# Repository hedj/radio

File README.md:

radio
=====

A minimal software-defined radio, based on the GreenArrays GA144A12 microprocessor.
Provision is made for connection to a Raspberry Pi B+ and shields. The GA144 analog
i/o pins are brought out to pin-headers to allow for different choices of RF frontends.

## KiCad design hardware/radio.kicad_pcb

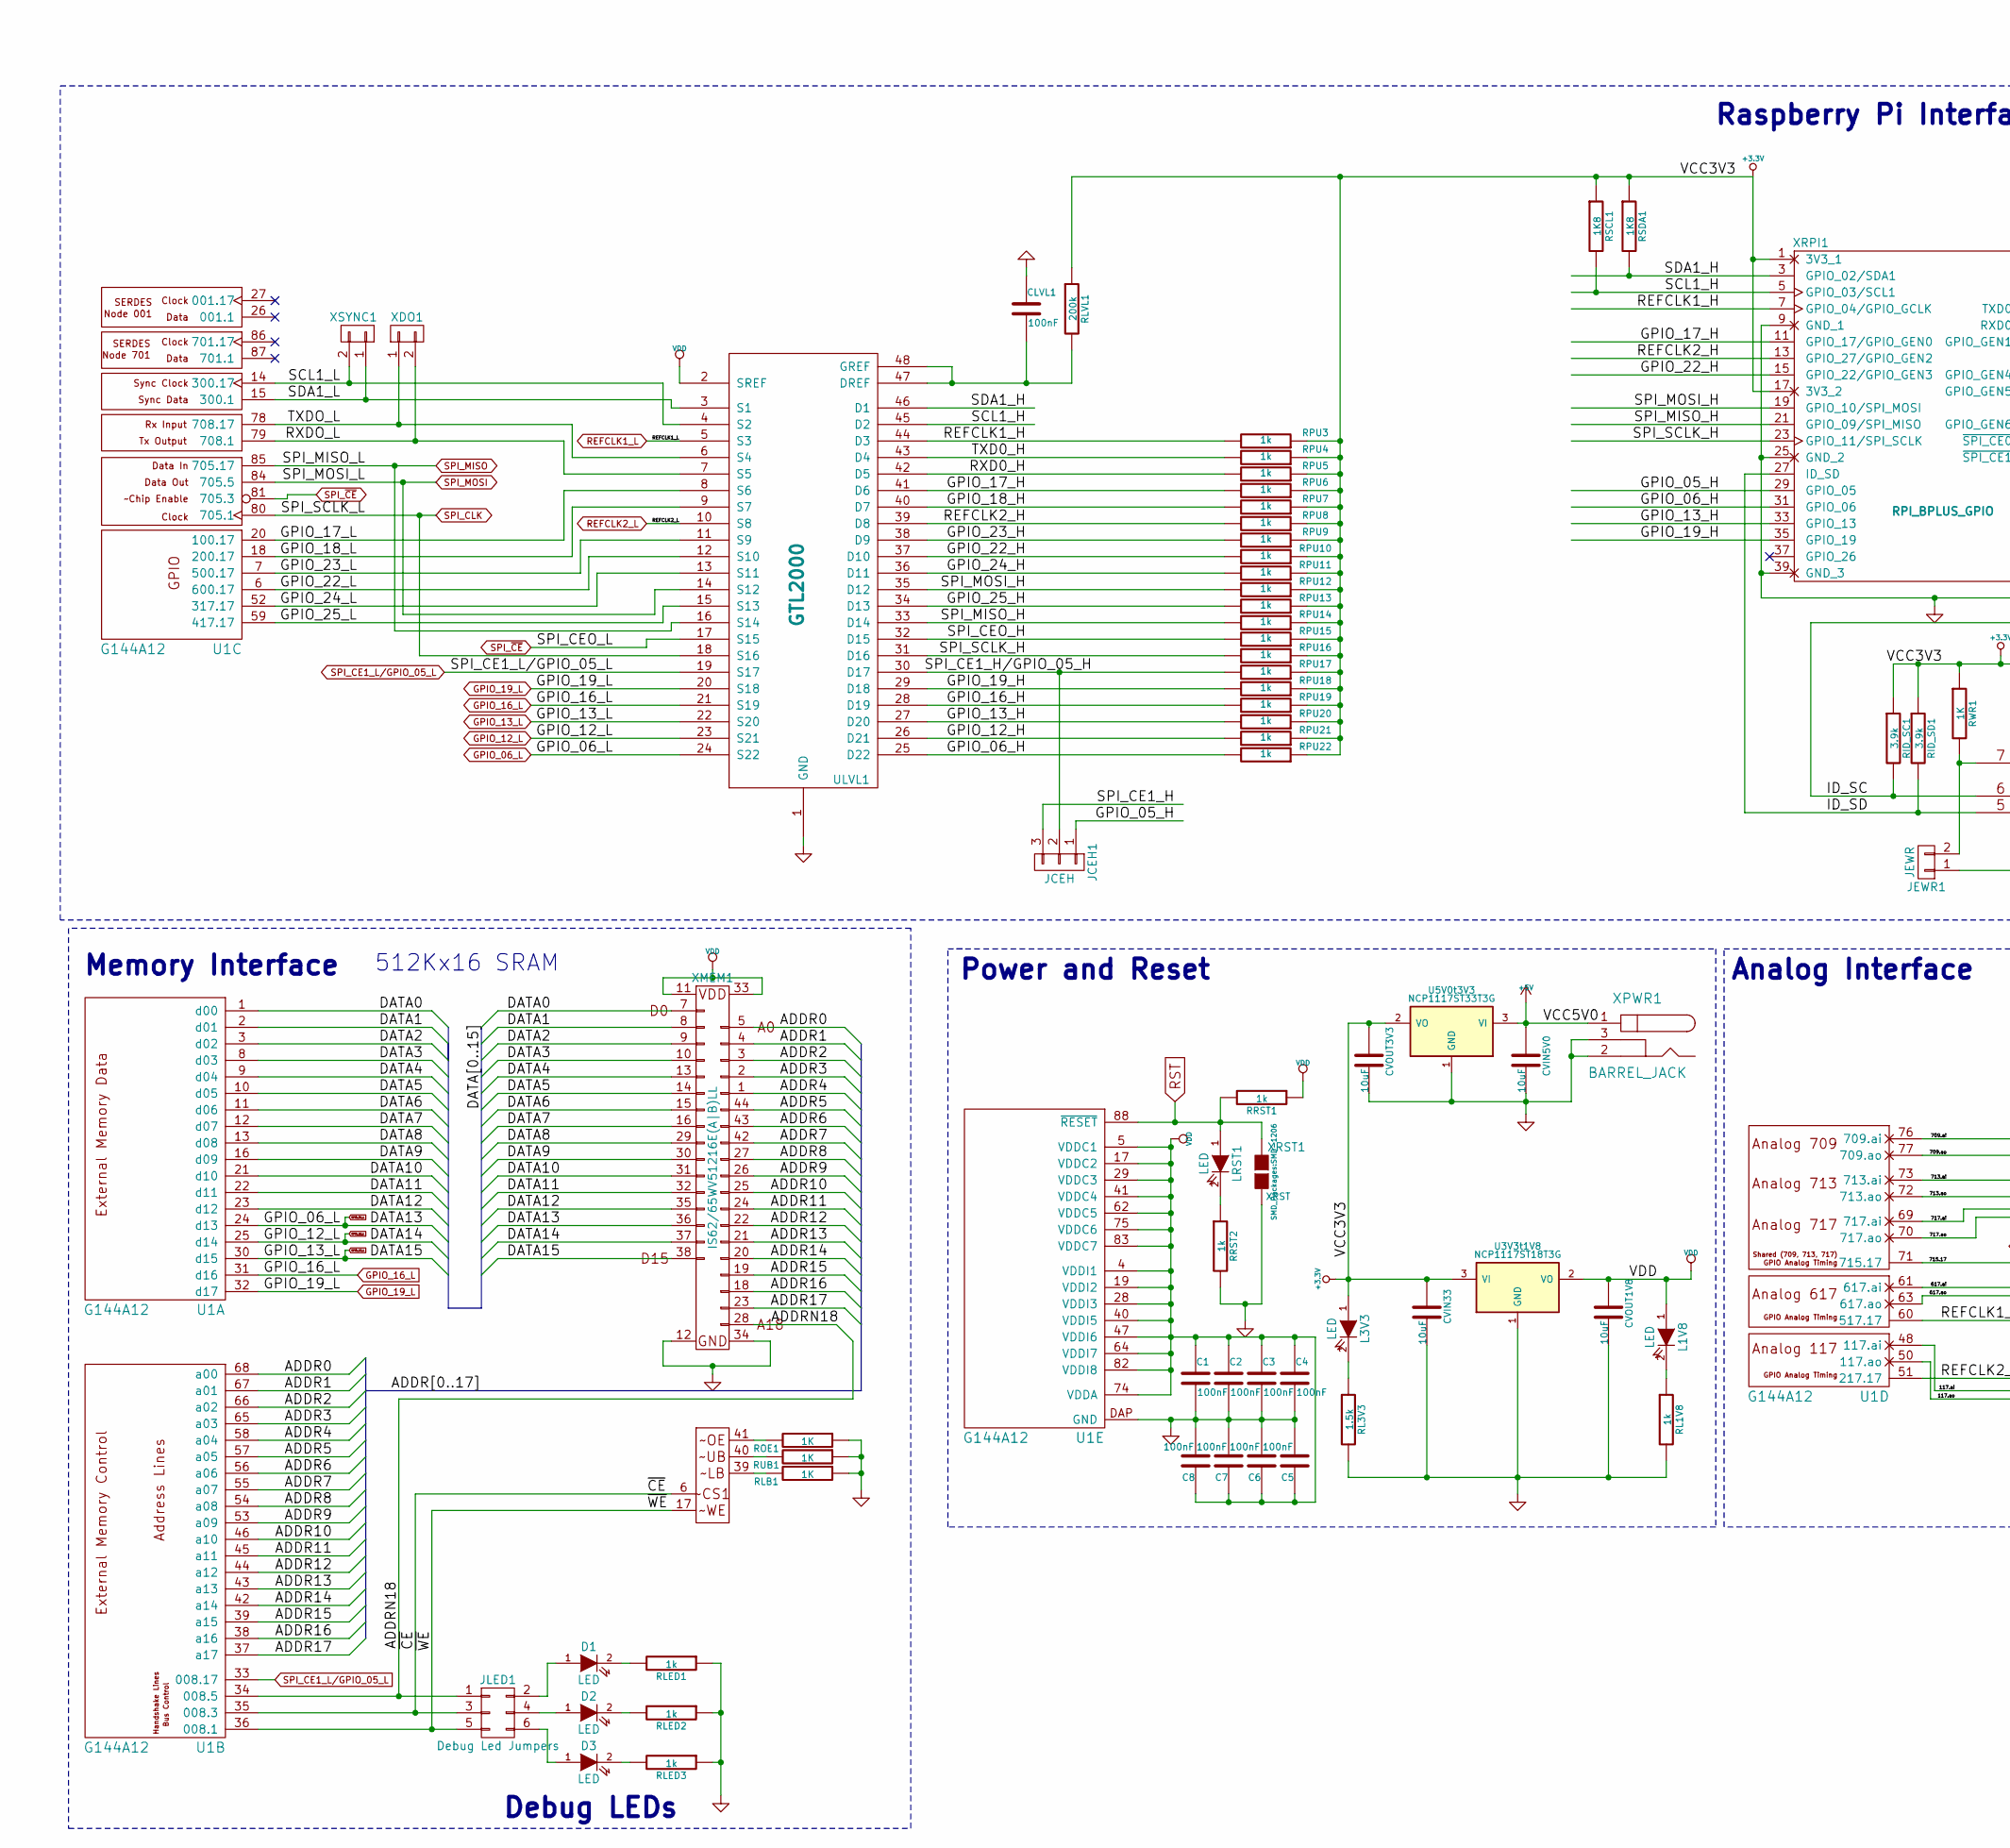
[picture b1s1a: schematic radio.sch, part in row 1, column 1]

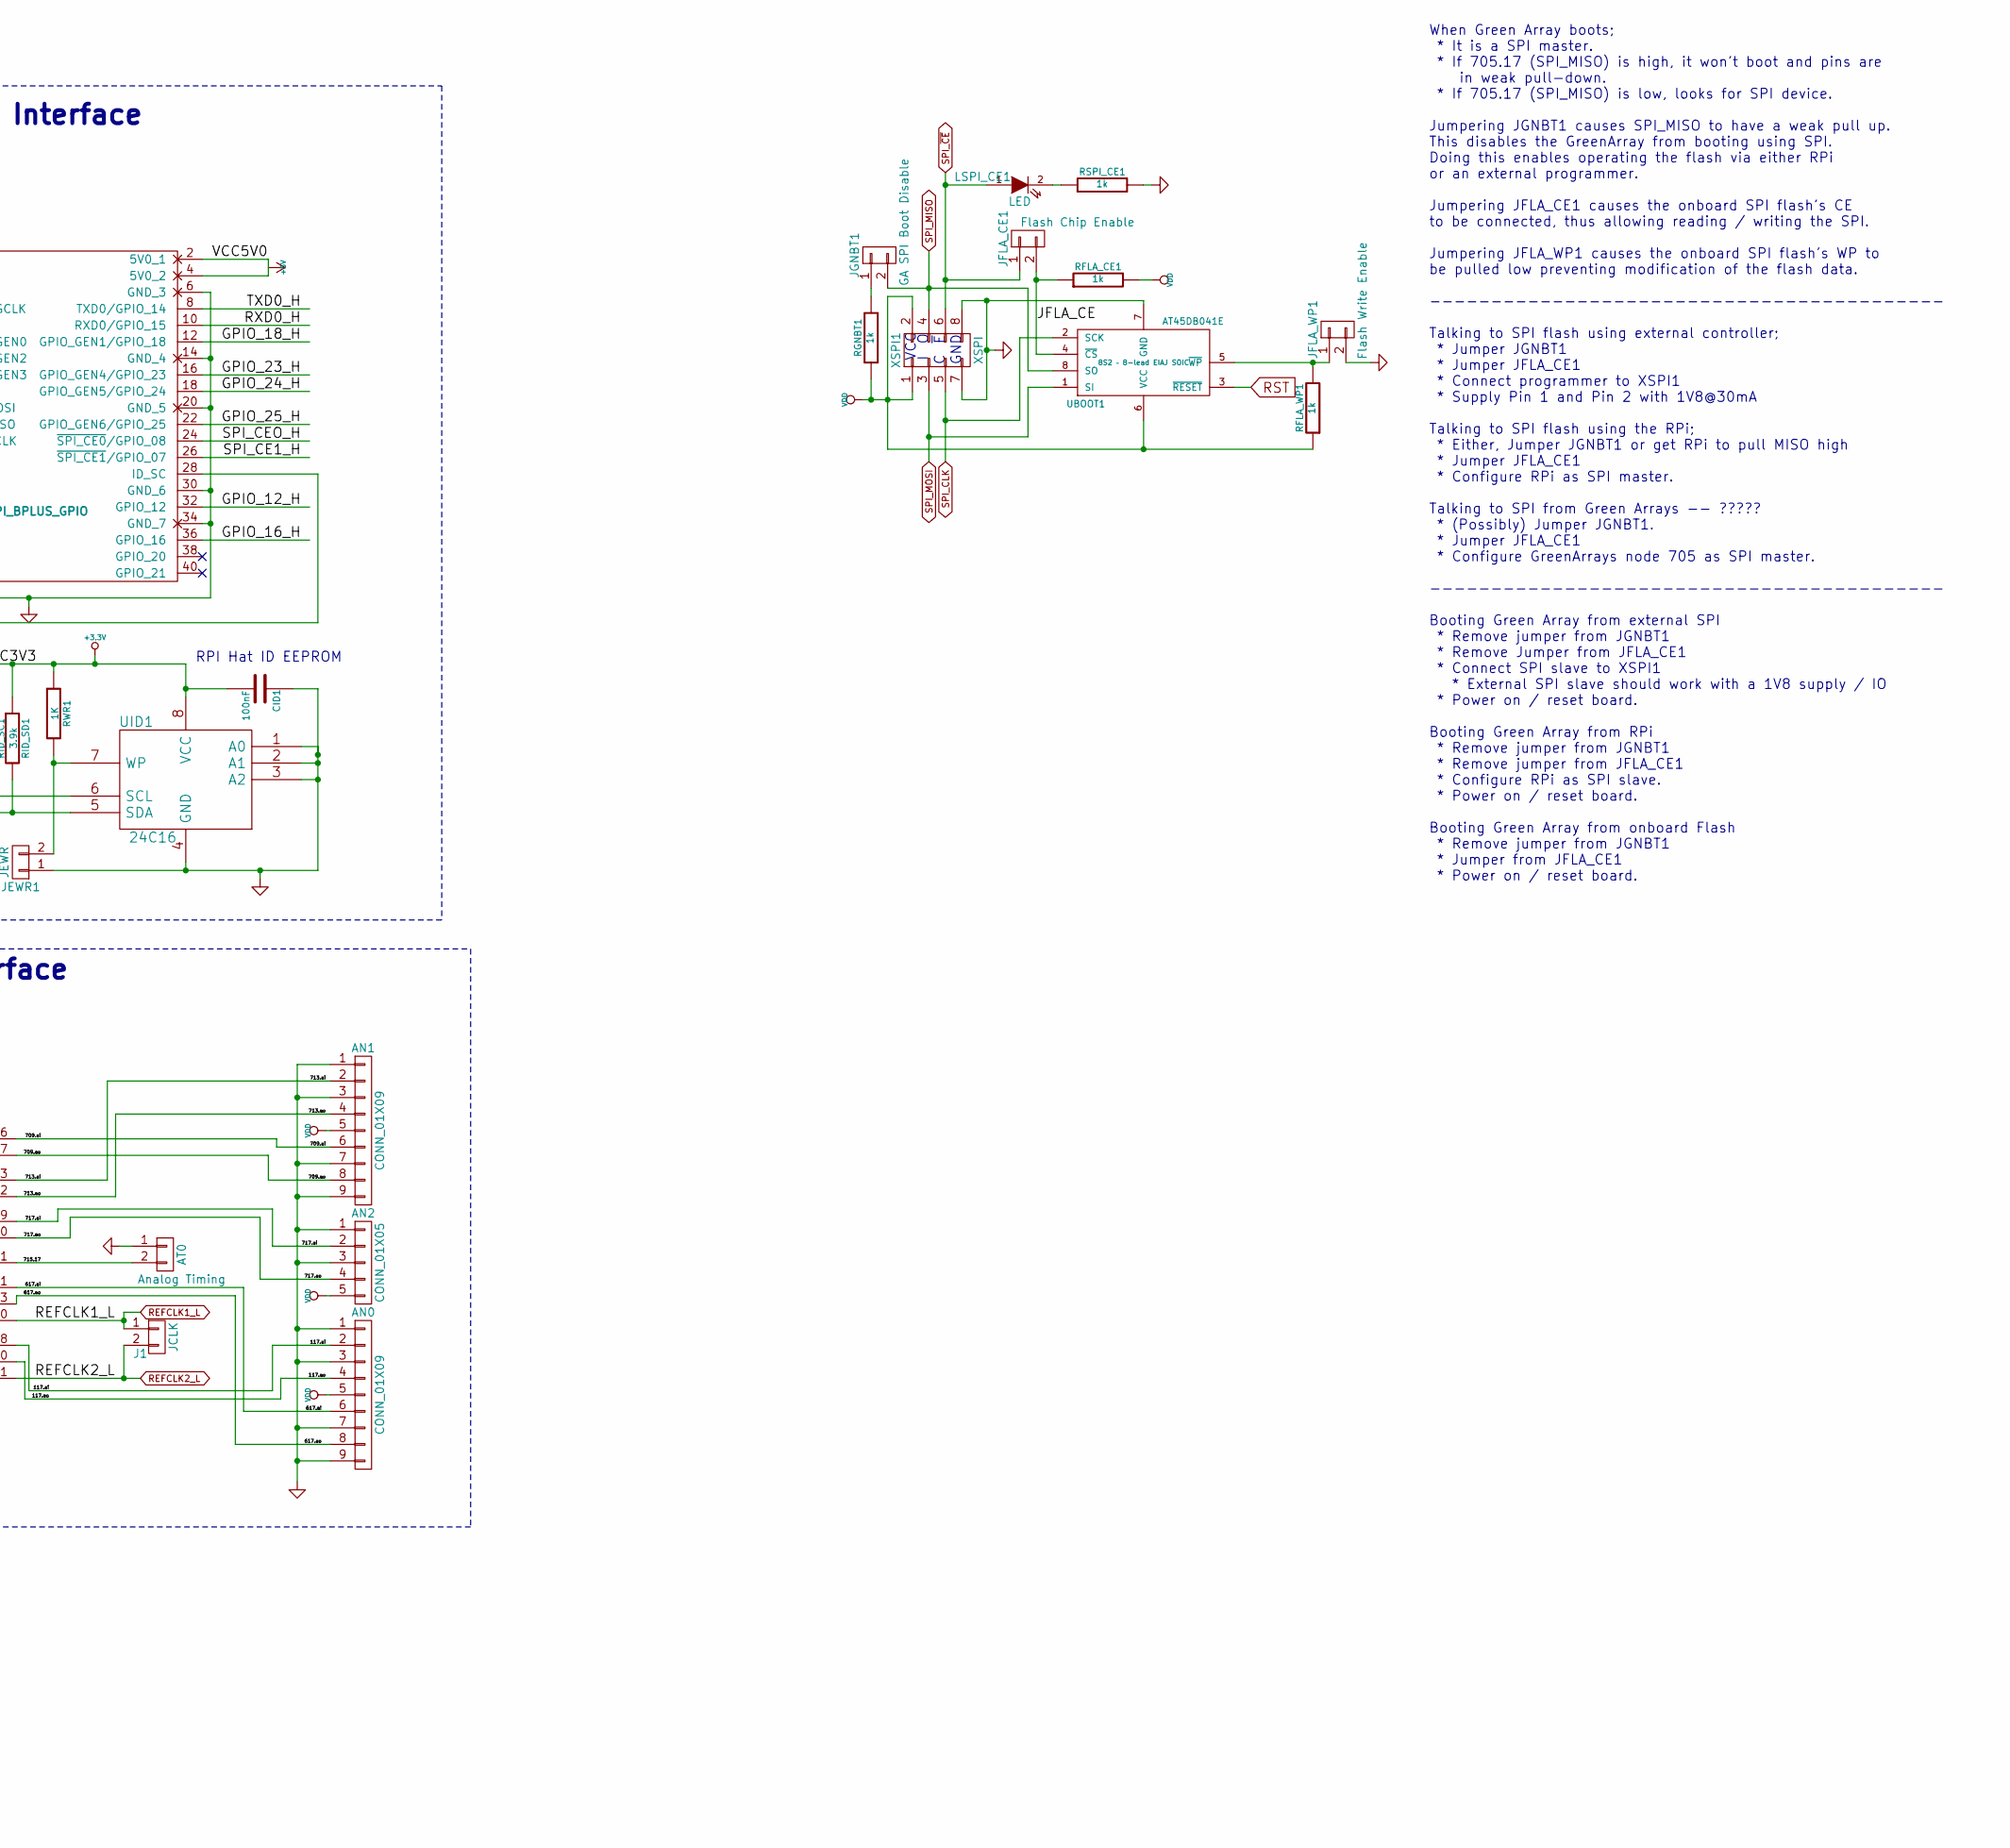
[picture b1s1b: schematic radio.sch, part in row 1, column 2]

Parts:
AN0, AN1: CONN_01X09; Pin_Header_Straight_1x09
AN2: CONN_01X05; Pin_Header_Straight_1x05
AT0: Analog Timing; Pin_Header_Straight_1x02
C1, C2, C3, C4, C5, C6, C7, C8: 100nF; SMD-0603
CID1: 100nF; SMD-0603
CLVL1: 100nF; SMD-0603
CVIN5V0, CVIN33: 10uF; SMD-0805
CVOUT1V8, CVOUT3V3: 10uF; SMD-0805
D1, D2, D3: LED; LED-0805
J1: JCLK; Pin_Header_Straight_1x02
JCEH1: JCEH; Pin_Header_Straight_1x03
JEWR1: JEWR; Pin_Header_Straight_1x02
JFLA_CE1: Flash Chip Enable; Pin_Header_Straight_1x02
JFLA_WP1: Flash Write Enable; Pin_Header_Straight_1x02
JGNBT1: GA SPI Boot Disable; Pin_Header_Straight_1x02
JLED1: Debug Led Jumpers; Pin_Header_Straight_2x03
L1V8, L3V3: LED; LED-0805
LRST1: LED; LED-0805
LSPI_CE1: LED; LED-0805
RFLA_CE1: 1k; R_0603
RFLA_WP1: 1k; R_0603
RGNBT1: 1k; R_0603
RID_SC1: 3.9k; R_0603
RID_SD1: 3.9k; R_0603
RL1V8: 1k; R_0603
RL3V3: 1.5k; R_0603
RLB1: 1K; R_0603
RLED1, RLED2, RLED3: 1k; R_0603
RLVL1: 200k; R_0603
ROE1: 1K; R_0603
RPU3, RPU4, RPU5, RPU6, RPU7, RPU8, RPU9, RPU10, RPU11, RPU12, RPU13, RPU14, RPU15, RPU16, RPU17, RPU18, RPU19, RPU20, RPU21, RPU22: 1k; R_0603
RRST1, RRST2: 1k; R_0603
RSCL1: 1K8; R_0603
RSDA1: 1K8; R_0603
RSPI_CE1: 1k; R_0603
RUB1: 1K; R_0603
RWR1: 1K; R_0603
U1: G144A12; qfn88
U3V3t1V8: NCP1117ST18T3G; SOT-223
U5V0t3V3: NCP1117ST33T3G; SOT-223
UBOOT1: AT45DB041E; SOIC-8-N
UID1: 24C16; SOIC-8-N
ULVL1: GTL2000; TSSOP-48
XDO1: Pin_Header_Straight_1x02
XMEM1: IS62/65WV51216E(A|B)LL; TSSOPII-44_0.8mmPitch
XPWR1: BARREL_JACK
XRPI1: RPI_BPLUS_GPIO; PIN_20X2
XRST1: XRST; SMD-1206
XSPI1: XSPI; Pin_Header_Straight_2x04
XSYNC1: Pin_Header_Straight_1x02

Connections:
+3.3V: CID1.2, CVIN33.1, CVOUT3V3.1, L3V3.1 (A), RID_SC1.1, RID_SD1.1, RLVL1.1, RPU3.1, RPU4.1, RPU5.1, RPU6.1, RPU7.1, RPU8.1, RPU9.1, RPU10.1, RPU11.1, RPU12.1, RPU13.1, RPU14.1, RPU15.1, RPU16.1, RPU17.1, RPU18.1, RPU19.1, RPU20.1, RPU21.1, RPU22.1, RSCL1.1, RSDA1.1, RWR1.1, U3V3t1V8.3 (VI), U5V0t3V3.2 (VO), U5V0t3V3.4, UID1.8 (VCC), XRPI1.1 (3V3_1), XRPI1.17 (3V3_2)
+5V: CVIN5V0.1, U5V0t3V3.3 (VI), XPWR1.1, XRPI1.2 (5V0_1), XRPI1.4 (5V0_2)
/117.ai: AN0.2, U1.48 (117.ai)
/117.ao: AN0.4, U1.50 (117.ao)
/617.ai: AN0.6, U1.61 (617.ai)
/617.ao: AN0.8, U1.63 (617.ao)
/709.ai: AN1.6, U1.76 (709.ai)
/709.ao: AN1.8, U1.77 (709.ao)
/713.ai: AN1.2, U1.73 (713.ai)
/713.ao: AN1.4, U1.72 (713.ao)
/715.17: AT0.2, U1.71 (715.17)
/717.ai: AN2.2, U1.69 (717.ai)
/717.ao: AN2.4, U1.70 (717.ao)
/ADDR0: U1.68 (a00), XMEM1.5
/ADDR1: U1.67 (a01), XMEM1.4
/ADDR2: U1.66 (a02), XMEM1.3
/ADDR3: U1.65 (a03), XMEM1.2
/ADDR4: U1.58 (a04), XMEM1.1
/ADDR5: U1.57 (a05), XMEM1.44
/ADDR6: U1.56 (a06), XMEM1.43
/ADDR7: U1.55 (a07), XMEM1.42
/ADDR8: U1.54 (a08), XMEM1.27
/ADDR9: U1.53 (a09), XMEM1.26
/ADDR10: U1.46 (a10), XMEM1.25
/ADDR11: U1.45 (a11), XMEM1.24
/ADDR12: U1.44 (a12), XMEM1.22
/ADDR13: U1.43 (a13), XMEM1.21
/ADDR14: U1.42 (a14), XMEM1.20
/ADDR15: U1.39 (a15), XMEM1.19
/ADDR16: U1.38 (a16), XMEM1.18
/ADDR17: U1.37 (a17), XMEM1.23
/ADDRN18: JLED1.1, U1.34 (008.5), XMEM1.28
/DATA0: U1.1 (d00), XMEM1.7
/DATA1: U1.2 (d01), XMEM1.8
/DATA2: U1.3 (d02), XMEM1.9
/DATA3: U1.8 (d03), XMEM1.10
/DATA4: U1.9 (d04), XMEM1.13
/DATA5: U1.10 (d05), XMEM1.14
/DATA6: U1.11 (d06), XMEM1.15
/DATA7: U1.12 (d07), XMEM1.16
/DATA8: U1.13 (d08), XMEM1.29
/DATA9: U1.16 (d09), XMEM1.30
/DATA10: U1.21 (d10), XMEM1.31
/DATA11: U1.22 (d11), XMEM1.32
/DATA12: U1.23 (d12), XMEM1.35
/GPIO_05_H: JCEH1.1, XRPI1.29 (GPIO_05)
/GPIO_06_H: RPU22.2, ULVL1.25 (D22), XRPI1.31 (GPIO_06)
/GPIO_12_H: RPU21.2, ULVL1.26 (D21), XRPI1.32 (GPIO_12)
/GPIO_13_H: RPU20.2, ULVL1.27 (D20), XRPI1.33 (GPIO_13)
/GPIO_16_H: RPU19.2, ULVL1.28 (D19), XRPI1.36 (GPIO_16)
/GPIO_17_H: RPU6.2, ULVL1.41 (D6), XRPI1.11 (GPIO_17/GPIO_GEN0)
/GPIO_17_L: U1.20 (100.17), ULVL1.8 (S6)
/GPIO_18_H: RPU7.2, ULVL1.40 (D7), XRPI1.12 (GPIO_GEN1/GPIO_18)
/GPIO_18_L: U1.18 (200.17), ULVL1.9 (S7)
/GPIO_19_H: RPU18.2, ULVL1.29 (D18), XRPI1.35 (GPIO_19)
/GPIO_22_H: RPU10.2, ULVL1.37 (D10), XRPI1.15 (GPIO_22/GPIO_GEN3)
/GPIO_22_L: U1.6 (600.17), ULVL1.12 (S10)
/GPIO_23_H: RPU9.2, ULVL1.38 (D9), XRPI1.16 (GPIO_GEN4/GPIO_23)
/GPIO_23_L: U1.7 (500.17), ULVL1.11 (S9)
/GPIO_24_H: RPU11.2, ULVL1.36 (D11), XRPI1.18 (GPIO_GEN5/GPIO_24)
/GPIO_24_L: U1.52 (317.17), ULVL1.13 (S11)
/GPIO_25_H: RPU13.2, ULVL1.34 (D13), XRPI1.22 (GPIO_GEN6/GPIO_25)
/GPIO_25_L: U1.59 (417.17), ULVL1.15 (S13)
/ID_SC: RID_SC1.2, UID1.6 (SCL), XRPI1.28 (ID_SC)
/ID_SD: RID_SD1.2, UID1.5 (SDA), XRPI1.27 (ID_SD)
/JFLA_CE: JFLA_CE1.2, RFLA_CE1.1, UBOOT1.4 (~CS)
/REFCLK1_H: RPU3.2, ULVL1.44 (D3), XRPI1.7 (GPIO_04/GPIO_GCLK)
/REFCLK2_H: RPU8.2, ULVL1.39 (D8), XRPI1.13 (GPIO_27/GPIO_GEN2)
/RXD0_H: RPU5.2, ULVL1.42 (D5), XRPI1.10 (RXD0/GPIO_15)
/RXDO_L: U1.79 (708.1), ULVL1.7 (S5), XDO1.2
/SCL1_H: RSCL1.2, ULVL1.45 (D2), XRPI1.5 (GPIO_03/SCL1)
/SCL1_L: U1.14 (300.17), ULVL1.4 (S2), XSYNC1.2
/SDA1_H: RSDA1.2, ULVL1.46 (D1), XRPI1.3 (GPIO_02/SDA1)
/SDA1_L: U1.15 (300.1), ULVL1.3 (S1), XSYNC1.1
/SPI_CE1_H: JCEH1.3, XRPI1.26 (~SPI_CE1~/GPIO_07)
/SPI_CE1_H/GPIO_05_H: JCEH1.2, RPU17.2, ULVL1.30 (D17)
/SPI_CEO_H: RPU15.2, ULVL1.32 (D15), XRPI1.24 (~SPI_CE0~/GPIO_08)
/SPI_MISO_H: RPU14.2, ULVL1.33 (D14), XRPI1.21 (GPIO_09/SPI_MISO)
/SPI_MOSI_H: RPU12.2, ULVL1.35 (D12), XRPI1.19 (GPIO_10/SPI_MOSI)
/SPI_SCLK_H: RPU16.2, ULVL1.31 (D16), XRPI1.23 (GPIO_11/SPI_SCLK)
/TXD0_H: RPU4.2, ULVL1.43 (D4), XRPI1.8 (TXD0/GPIO_14)
/TXDO_L: U1.78 (708.17), ULVL1.6 (S4), XDO1.1
/~CE: JLED1.3, U1.35 (008.3), XMEM1.6
/~WE: JLED1.5, U1.36 (008.1), XMEM1.17
GND: AN0.1, AN0.3, AN0.7, AN0.9, AN1.1, AN1.3, AN1.7, AN1.9, AN2.1, AN2.3, AT0.1, C1.2, C2.2, C3.2, C4.2, C5.2, C6.2, C7.2, C8.2, CID1.1, CLVL1.1, CVIN5V0.2, CVIN33.2, CVOUT1V8.2, CVOUT3V3.2, JEWR1.1, JFLA_WP1.2, RL1V8.2, RL3V3.2, RLB1.1, RLED1.1, RLED2.1, RLED3.1, ROE1.1, RRST2.2, RSPI_CE1.2, RUB1.1, U1.DAP (GND), U3V3t1V8.1 (GND), U5V0t3V3.1 (GND), UBOOT1.7 (GND), UID1.1 (A0), UID1.2 (A1), UID1.3 (A2), UID1.4 (GND), ULVL1.1 (GND), XMEM1.12, XMEM1.34, XPWR1.2, XPWR1.3, XRPI1.6 (GND_3), XRPI1.9 (GND_1), XRPI1.14 (GND_4), XRPI1.20 (GND_5), XRPI1.25 (GND_2), XRPI1.30 (GND_6), XRPI1.34 (GND_7), XRPI1.39 (GND_3), XRST1.2 (G2), XSPI1.7, XSPI1.8
GPIO_06_L: U1.24 (d13), ULVL1.24 (S22), XMEM1.36
GPIO_12_L: U1.25 (d14), ULVL1.23 (S21), XMEM1.37
GPIO_13_L: U1.30 (d15), ULVL1.22 (S20), XMEM1.38
GPIO_16_L: U1.31 (d16), ULVL1.21 (S19)
GPIO_19_L: U1.32 (d17), ULVL1.20 (S18)
unnamed: CLVL1.2, RLVL1.2, ULVL1.47 (DREF), ULVL1.48 (GREF)
unnamed: D1.1 (A), JLED1.2
unnamed: D1.2 (K), RLED1.2
unnamed: D2.1 (A), JLED1.4
unnamed: D2.2 (K), RLED2.2
unnamed: D3.1 (A), JLED1.6
unnamed: D3.2 (K), RLED3.2
unnamed: JEWR1.2, RWR1.2, UID1.7 (WP)
unnamed: JFLA_WP1.1, RFLA_WP1.2, UBOOT1.5 (~WP)
unnamed: JGNBT1.1, RGNBT1.2
unnamed: L1V8.2 (K), RL1V8.1
unnamed: L3V3.2 (K), RL3V3.1
unnamed: LRST1.2 (K), RRST2.1
unnamed: LSPI_CE1.2 (K), RSPI_CE1.1
unnamed: RLB1.2, XMEM1.39
unnamed: ROE1.2, XMEM1.41
unnamed: RUB1.2, XMEM1.40
REFCLK1_L: J1.1, U1.60 (517.17), ULVL1.5 (S3)
REFCLK2_L: J1.2, U1.51 (217.17), ULVL1.10 (S8)
RST: LRST1.1 (A), RRST1.2, U1.88 (~RESET), UBOOT1.3 (~RESET), XRST1.1 (G1)
SPI_CE1_L/GPIO_05_L: U1.33 (008.17), ULVL1.19 (S17)
SPI_CLK: U1.80 (705.1), UBOOT1.2 (SCK), ULVL1.18 (S16), XSPI1.5
SPI_MISO: JGNBT1.2, U1.85 (705.17), UBOOT1.8 (SO), ULVL1.16 (S14), XSPI1.4
SPI_MOSI: U1.84 (705.5), UBOOT1.1 (SI), ULVL1.14 (S12), XSPI1.3
SPI_~CE: JFLA_CE1.1, LSPI_CE1.1 (A), U1.81 (705.3), ULVL1.17 (S15), XSPI1.6
VDD: AN0.5, AN1.5, AN2.5, C1.1, C2.1, C3.1, C4.1, C5.1, C6.1, C7.1, C8.1, CVOUT1V8.1, L1V8.1 (A), RFLA_CE1.2, RFLA_WP1.1, RGNBT1.1, RRST1.1, U1.4 (VDDI1), U1.5 (VDDC1), U1.17 (VDDC2), U1.19 (VDDI2), U1.28 (VDDI3), U1.29 (VDDC3), U1.40 (VDDI5), U1.41 (VDDC4), U1.47 (VDDI6), U1.62 (VDDC5), U1.64 (VDDI7), U1.74 (VDDA), U1.75 (VDDC6), U1.82 (VDDI8), U1.83 (VDDC7), U3V3t1V8.2 (VO), U3V3t1V8.4, UBOOT1.6 (VCC), ULVL1.2 (SREF), XMEM1.11, XMEM1.33, XSPI1.1, XSPI1.2

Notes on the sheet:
Analog Interface
Power and Reset
Raspberry Pi Interface
Memory Interface
Debug LEDs
RPI Hat ID EEPROM
GND
VCC
512Kx16 SRAM
When Green Array boots; * It is a SPI master. * If 705.17 (SPI_MISO) is high, it won't boot and pins are in weak pull-down. * If 705.17 (SPI_MISO) is low, looks for SPI device. Jumpering JGNBT1 causes SPI_MISO to have a weak pull up. This disables the GreenArray from booting using SPI. Doing this e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

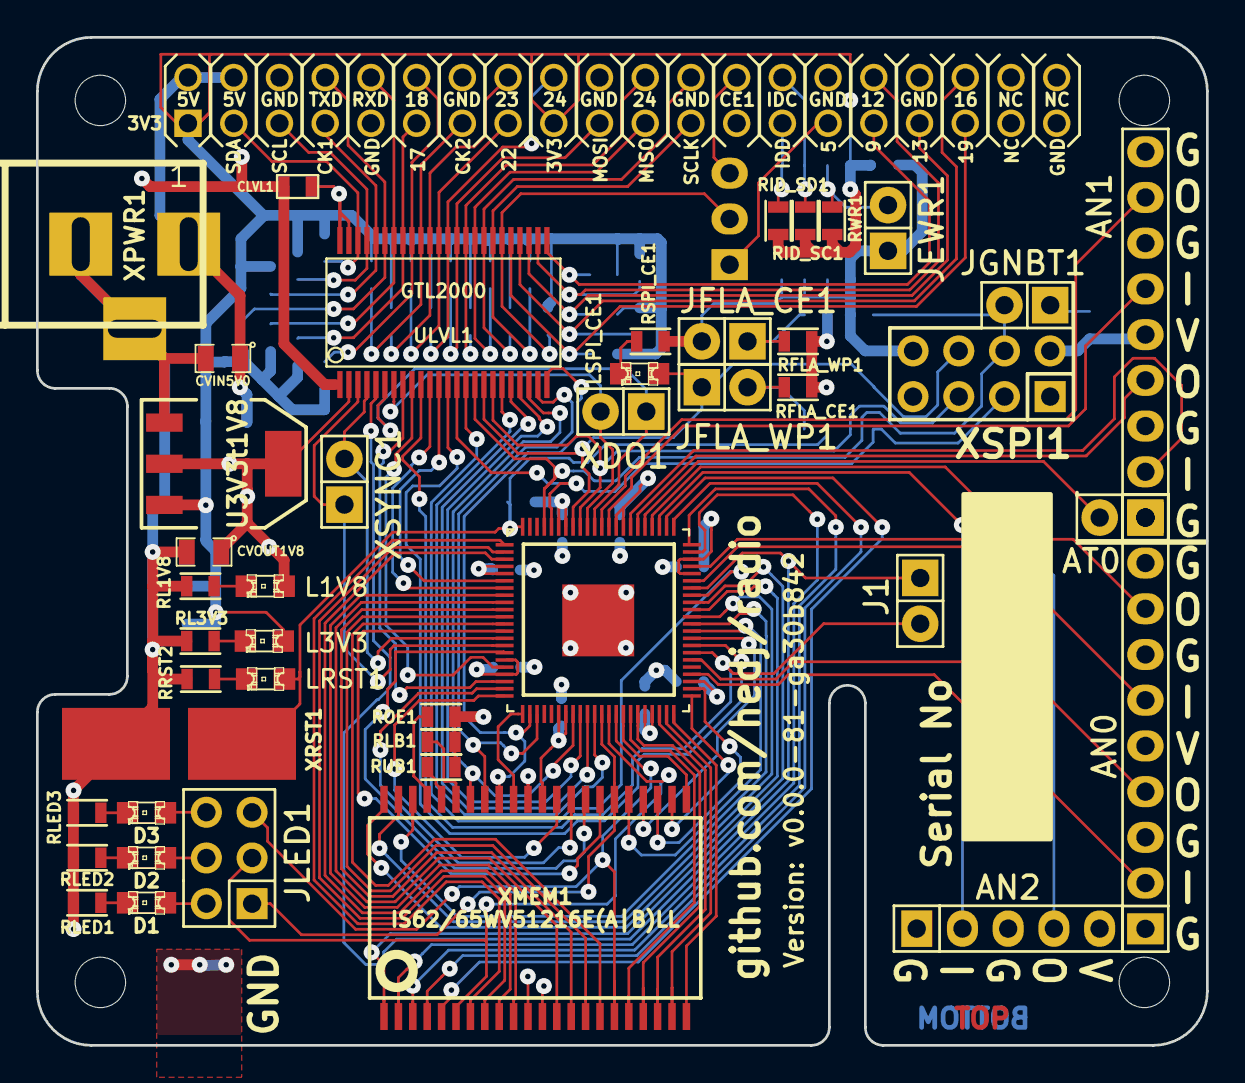
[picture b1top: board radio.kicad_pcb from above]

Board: 4 copper layers, 65.0 x 56.0 mm, 89 parts (0 on the bottom side), 116 nets.

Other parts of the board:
@HOLE0, @HOLE1, @HOLE2, @HOLE3: (no value)

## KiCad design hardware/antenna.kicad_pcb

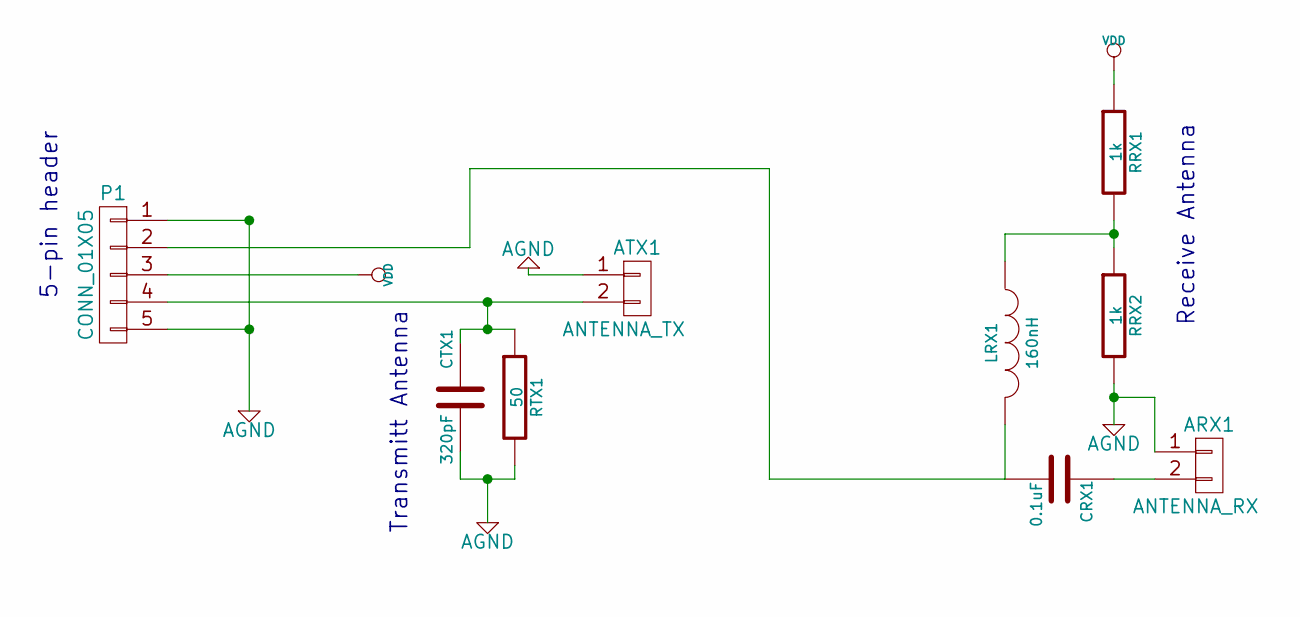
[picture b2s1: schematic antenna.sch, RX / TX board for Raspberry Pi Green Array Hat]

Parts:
ARX1: ANTENNA_RX; bnc
ATX1: ANTENNA_TX; bnc
CRX1: 0.1uF; SMD-0603
CTX1: 320pF; SMD-0603
LRX1: 160nH; SMD-0603
P1: CONN_01X05; Pin_Header_Straight_1x05
RRX1, RRX2: 1k; R_0603
RTX1: 50; R_0603

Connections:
AGND: ARX1.1, ATX1.1, CTX1.2, P1.1, P1.5, RRX2.2, RTX1.2
unnamed: ARX1.2, CRX1.1
unnamed: ATX1.2, CTX1.1, P1.4, RTX1.1
unnamed: CRX1.2, LRX1.2, P1.2
unnamed: LRX1.1, RRX1.2, RRX2.1
VDD: P1.3, RRX1.1

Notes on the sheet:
Receive Antenna
5-pin header
Transmitt Antenna

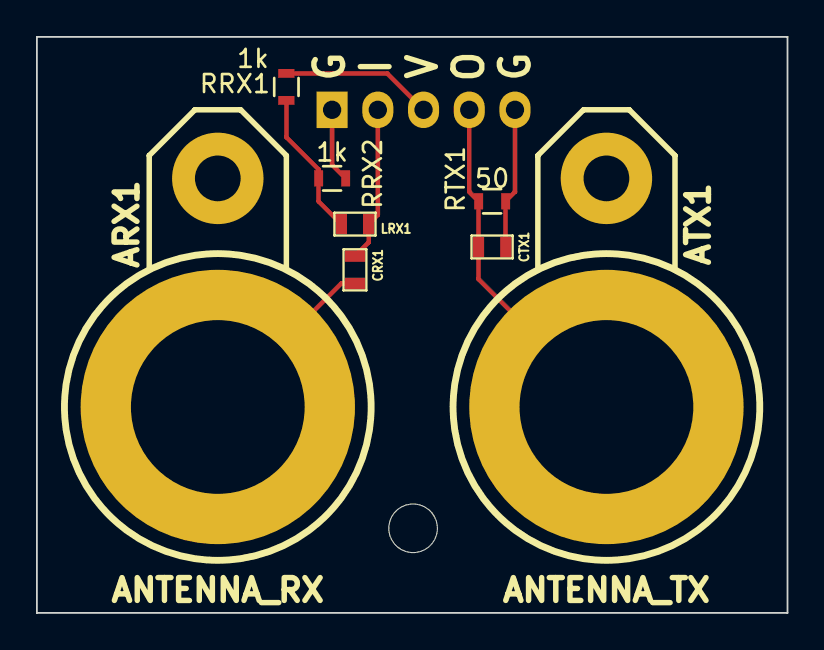
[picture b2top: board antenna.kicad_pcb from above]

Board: 2 copper layers, 41.7 x 32.0 mm, 10 parts (1 on the bottom side), 6 nets.

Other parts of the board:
MountingHole_2-7mm: VAL**; MountingHole_2-7mm

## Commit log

2014-09-09 Cleanup redundant and obsolete files
2014-09-09 Add garfc, remove redundant files.
2014-09-09 Add PDFs of schematics
2014-09-13 Fully created schematic and footprint associations.
2014-09-13 Partially routed schematic.
2014-09-13 Totally rework how the pull up resistors work.
2014-09-13 More routing of stuff.
2014-09-13 Minor fixes.
2014-09-14 Remove unused libraries.
2014-09-14 Swapping SDA and SCLK to make routing easier.
2014-09-15 Adding SPI flash and changing the SPI setup.
2014-10-18 Adding mini-PCI Express expansion board as dependency.
2014-11-01 Adding the SATA connector library.
2014-11-01 Temporary commit with latest updated.
2014-11-01 Moving the antenna onto its own board.
2014-11-01 Removing the antenna from the radio schematic.
2014-11-01 Preparing to hook up mPCIe connector and adding documentation.
2014-11-01 Lots of different fixes.
    * Removing mpcie and replacing with onboard memory (freeing up some pins).
    * Changing the SPI configuration (don't actually need the fancy 3 way header).
    Added lots of documentation how to work with SPI flash for booting,
    programming, etc.
    * Fixed all the electrical DRC errors.
2014-11-01 Adding a LED onto the SPI CE to make debugging easier.
2014-11-01 Removing mpcie from PCB library.
2014-11-01 Temporary commit.
2014-11-01 Use custom SATA connector for design-rule compatibility
2014-11-01 Adding SATA PCB module.
2014-11-01 Back to pin headers rather than SATA connectors.
2014-11-01 Bit of a cleanup, temporary commit.
2014-11-01 Fixing XSPI connector.
2014-11-01 Temporary commit for netlist import.
2014-11-01 Imported new netlist and lined up analog headers.
2014-11-01 Starting initial layout of parts.
2014-11-02 Initial PCB layout for antenna
2014-11-15 Fixing the ground plane fill.
2014-11-15 Adding dimensions of the antenna board.
2014-11-15 Adding dimensions to radio board.
2014-11-15 Placing the barrel jack and power supply.
2014-11-15 Temp commit.
2014-11-15 Using older 603 footprint.
2014-11-15 Getting LEDs and reset points right.
2014-11-15 More work.
2014-11-15 Slowly getting there....
2014-11-15 Reorganising the Analog header for easier routing.
2014-11-15 Analog bits connected now.
2014-11-15 Removing the XSERDES1 header.
2014-11-15 KiCad crashed :(
2014-11-15 Autosave.
2014-11-15 Finished most of the SPI stuff.
2014-11-15 Adding decoupling capacitors.
2014-11-15 Decoupling capacitors connected up.
2014-11-16 Adding the UART header.
2014-11-16 All traces routed I think.
2014-11-16 Lots of small fixes.
2014-11-30 Making clearance 0.15**24** and trace width 0.15**24**.
2014-11-30 4 layer design.
2014-11-30 More 4 layer work.
2014-11-30 More optimisation.
2015-03-07 Getting close to first production run.
2015-03-07 Fixing up the antenna board.
2015-03-11 Small fixes.
2015-03-21 Small adjustments from doing paper fit.
2015-06-03 Extending the solder pads for the RAM chip.
    Fixes #3.
2015-06-03 Fixing some vias.
2015-06-03 Updating schematic and adding link to connector.
2015-06-03 Making the qfn88 pads hand solderable.
    Fixes #5.
2015-06-03 Routing update.
    Also makes a huge pad for adding reset switches onto.
    Fixes #5 and #6.
2015-06-03 Small silkscreen updates.
2015-06-05 Fixing short on level shifter in top right hand corner.
2015-06-05 Adding raspberry pi labeling.
    Fixes #8.
2015-06-05 Fixing silkscreen issues.
2015-06-05 Adding more stuff to silk screen.
2015-06-05 Adding GND connection point for testing.
2015-06-05 More silkscreen updates.
2015-06-05 Adding openhardware logo.
2015-06-05 Fixing ground pad.
2015-06-05 Fix drill size for vias.
2015-06-05 Don't use extended gerbers
2015-06-05 First run gerbers.
2015-06-06 Small fixes from Mitch (@hackvana).
2015-06-06 Version bump.
2015-06-06 Updating the gerbers.
2015-06-19 Removing obsolete stuff.
2015-06-19 Remove old library.
2015-06-19 Fixing the values of the 1.8V connected LEDs.
2015-06-27 Fixing resistor values.
2015-06-27 Removing LED on the SPI Chip Enable line.
    This LED can't work because we need a pull up via 1k resistor which we can't
    replace with 100 ohm as the GreenArray's needs to be able to pull it down.
2015-06-27 Removing more unused files.
2015-06-27 Start of EEPROM contents needed by RPi.
2015-06-28 Renaming J1 to XCLK1 to be consistent with other headers.
2015-07-12 Beginnings of an assembler.
2015-07-12 Update comment to reflect purpose
2016-08-03 Gerber's zip file actually produced.
